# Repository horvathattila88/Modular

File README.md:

# Modular
Modular synth stuff

Most of these are designs from other people, i've just redrawn them to fit into a eurorack system. The PCB's are smaller than 100x100mm, so it's easier to have them manufactured, pick any of your favourite manufacturers. The plans are in EAGLE 7.4 format, you can generate gerbers from there, according to the manufacturers needs. 
I have uploaded this for hobbyists, i don't make any money out of it, you shouldn't sell the boards! 
The MFOS ones are designed by Ray Wilson - Music From Outer Space, please respect his heritage. 
Yusynth is Yves Usson

The PSU is my own design, (simple as Trump) you'll need a transformer with 2x12V AC secondaries, or 1x15V AC, connected to the center and one of the AC inputs. Two way, or one way rectifier, you choose, i like to use 2-way, with a center tap transformer. 
Don't use it for more than 7-800mA, for example, one bigger transformer on the bottom of the case and one PSU in each row... Install the SMD or the TH LED's, not both. There is no 5V rail, nor CV, or Gate, as i'm not using those, and found it's a bad solution. 
There is also a distribution board, it can be cut into more strips if needed. LED's and filtering caps can be soldered on those too, but not necessary. 

Part numbering is (most of the time) the same as in the MFOS webpage, you'll need to read through the documentation there. 
There are some exceptions, like the ringmodulator, i've made a dual ringmod without the VC sine osc, and the simple osc on a standalone module. It's quite straightforward though. 

Here is the status of the modules: 

PSU, rails - Tested OK, pinouts are the same as on the modules, be careful when making ribbon cables! 

MFOS VCF 12dBi state variable - Tested OK (sounds sweet) 

MFOS VC LFO - Tested OK 

MFOS VCO - Tested, not calibrated yet

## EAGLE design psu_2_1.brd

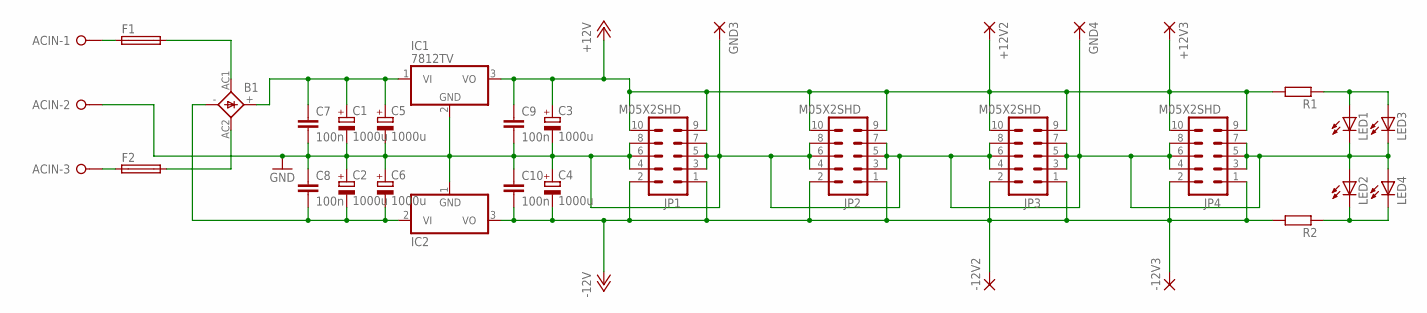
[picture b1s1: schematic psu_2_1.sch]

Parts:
+12V2, +12V3: 2,54/1,0
-12V2, -12V3: 2,54/1,0
ACIN: W237-3E
B1: 2KBP
C1, C2, C3, C4, C5, C6: 1000u; E3,5-10
C7, C8, C9, C10: 100n; C1206K
F1, F2: 19560
GND3, GND4: 2,54/1,0
IC1: 7812TV; TO220V
IC2: 7912TV; TO220V
JP1, JP2, JP3, JP4: M05X2SHD; 2X5-SHROUDED
LED1, LED2: LED3MM
LED3, LED4: LEDCHIPLED_1206; CHIPLED_1206
R1, R2: R-EU_M1206; M1206

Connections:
+12V: +12V2.1, +12V3.1, C3.+, C9.1, IC1.3 (VO), JP1.9, JP1.10, JP2.9, JP2.10, JP3.9, JP3.10, JP4.9, JP4.10, R1.2
-12V: -12V2.1, -12V3.1, C4.-, C10.2, IC2.3 (VO), JP1.1, JP1.2, JP2.1, JP2.2, JP3.1, JP3.2, JP4.1, JP4.2, R2.2
GND: ACIN.2, C1.-, C2.+, C3.-, C4.+, C5.-, C6.+, C7.2, C8.1, C9.2, C10.1, GND3.1, GND4.1, IC1.2 (GND), IC2.1 (GND), JP1.3, JP1.4, JP1.5, JP1.6, JP1.7, JP1.8, JP2.3, JP2.4, JP2.5, JP2.6, JP2.7, JP2.8, JP3.3, JP3.4, JP3.5, JP3.6, JP3.7, JP3.8, JP4.3, JP4.4, JP4.5, JP4.6, JP4.7, JP4.8, LED1.K (C), LED2.A, LED3.C, LED4.A
unnamed: LED2.K (C), LED4.C, R2.1
unnamed: LED1.A, LED3.A, R1.1
unnamed: B1.-, C2.-, C6.-, C8.2, IC2.2 (VI)
unnamed: B1.+, C1.+, C5.+, C7.1, IC1.1 (VI)
unnamed: B1.AC1, F1.2
unnamed: B1.AC2, F2.2
unnamed: ACIN.1, F1.1
unnamed: ACIN.3, F2.1

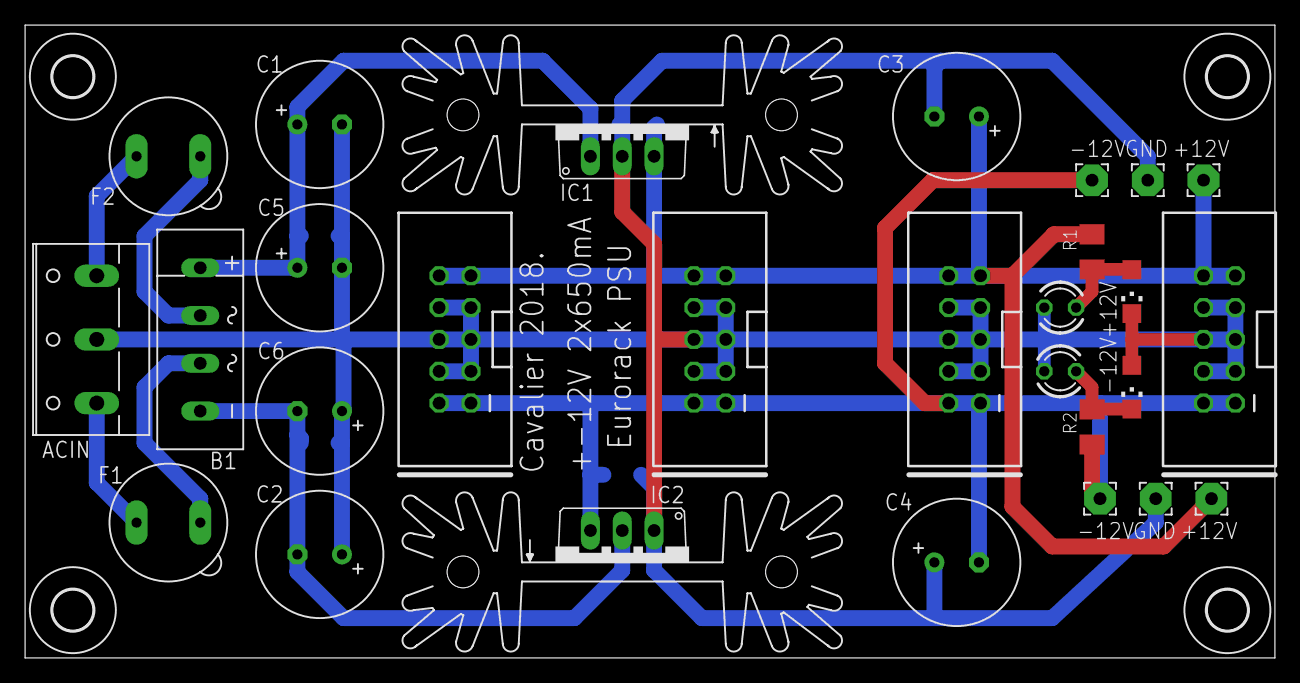
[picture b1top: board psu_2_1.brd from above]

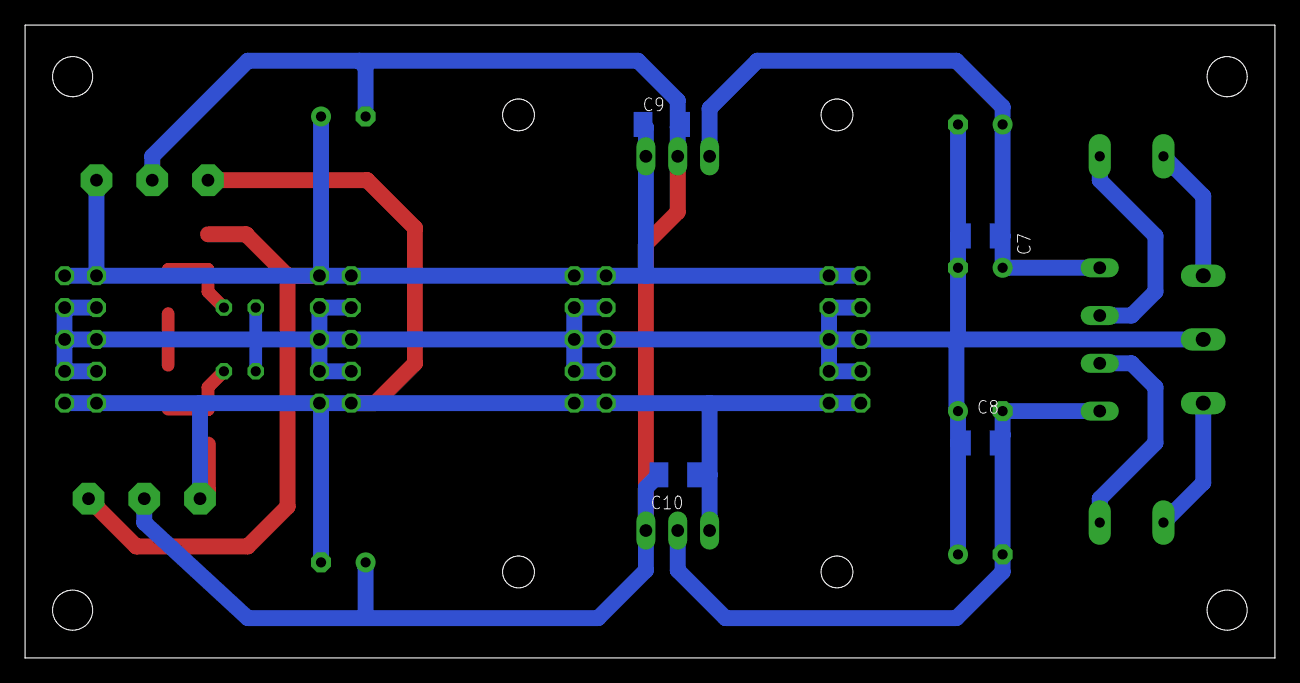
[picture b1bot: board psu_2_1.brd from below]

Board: 2 copper layers, 99.7 x 50.5 mm, 38 parts (4 on the bottom side), 11 nets.

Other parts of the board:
U$1, U$2, U$3, U$4: 3,2
U$5, U$7: SK104

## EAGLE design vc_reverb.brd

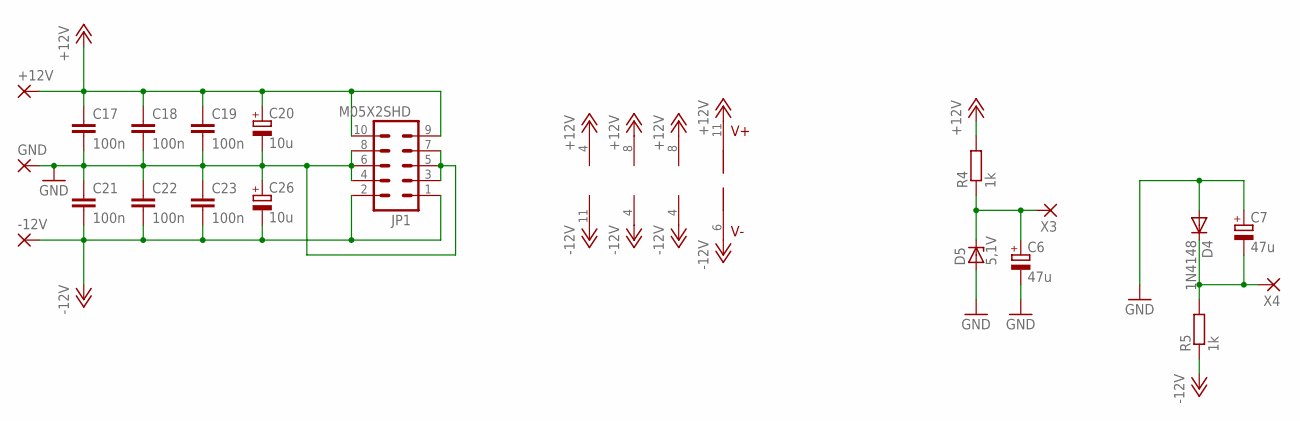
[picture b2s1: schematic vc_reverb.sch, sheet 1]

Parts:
+12V: 2,54/1,0
-12V: 2,54/1,0
C6, C7: 47u; E2-5
C17, C19, C21, C23: 100n; C025-025X050
C18, C22: 100n; C050-035X075
C20, C26: 10u; E2-5
D4: 1N4148; DO35-7
D5: 5,1V; DO34Z7
GND: 2,54/1,0
IC3: TL074P; DIL14
IC4: LM13700N; DIL16
IC5, IC6: TL072P; DIL08
JP1: M05X2SHD; 2X5-SHROUDED
R4, R5: 1k; 0309V
X3, X4: 2,54/1,0

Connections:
+12V: +12V.1, C17.1, C18.1, C19.1, C20.+, IC3.4 (V+), IC4.11 (V+), IC5.8 (V+), IC6.8 (V+), JP1.9, JP1.10, R4.2; also elsewhere on the board
-12V: -12V.1, C21.2, C22.2, C23.2, C26.-, IC3.11 (V-), IC4.6 (V-), IC5.4 (V-), IC6.4 (V-), JP1.1, JP1.2, R5.1; also elsewhere on the board
GND: C6.-, C7.+, C17.2, C18.2, C19.2, C20.-, C21.1, C22.1, C23.1, C26.+, D4.A, D5.A, GND.1, JP1.3, JP1.4, JP1.5, JP1.6, JP1.7, JP1.8; also elsewhere on the board
unnamed: C6.+, D5.C, R4.1, X3.1
unnamed: C7.-, D4.C, R5.2, X4.1

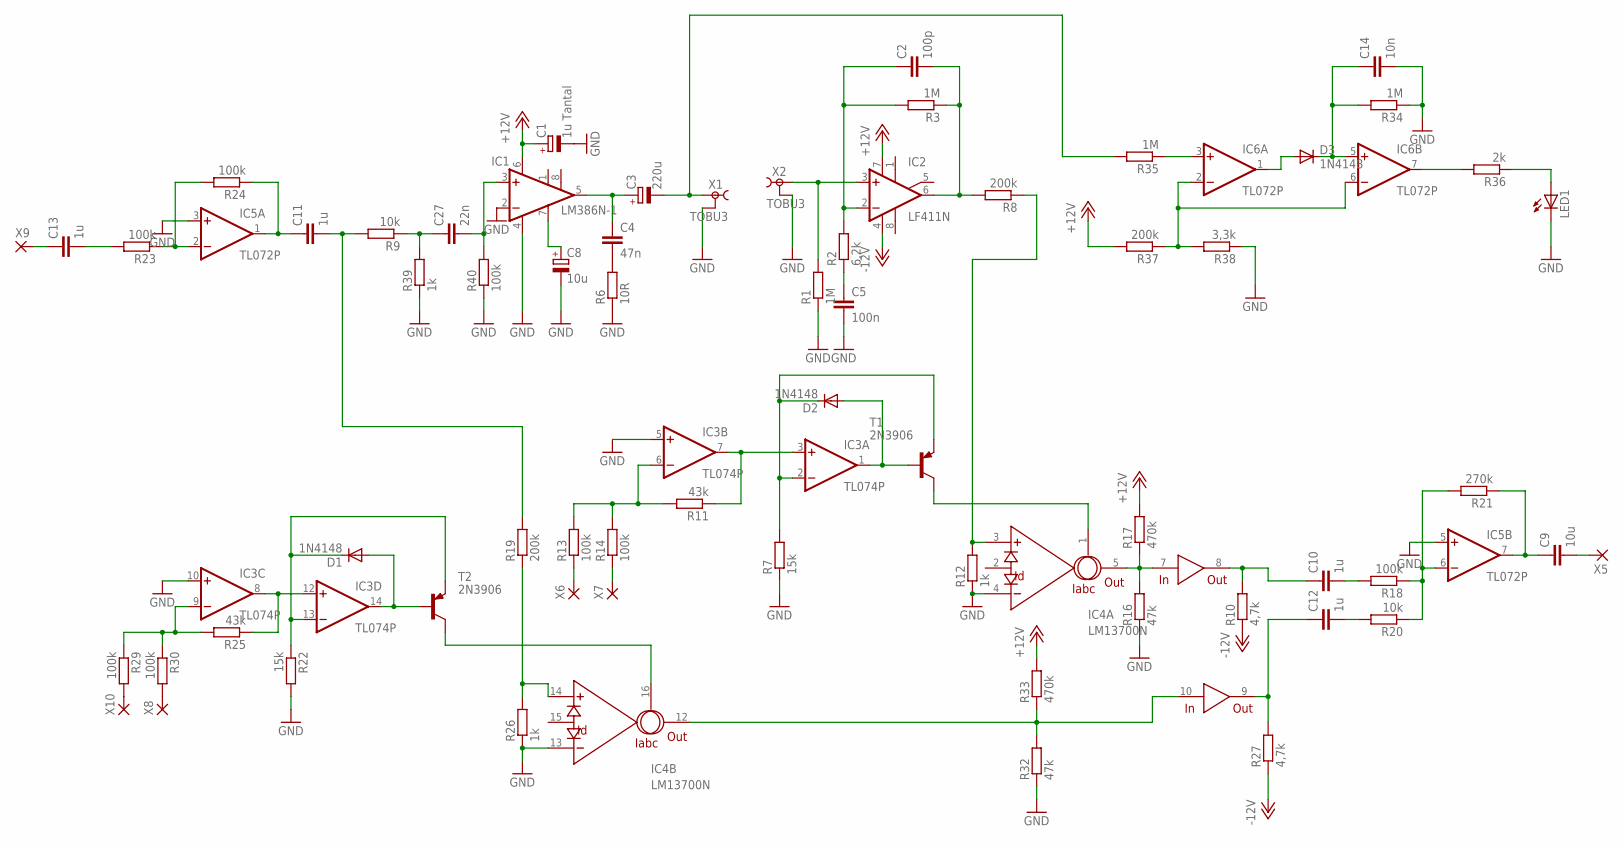
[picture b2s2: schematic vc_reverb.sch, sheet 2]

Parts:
C1: 1u Tantal; E2-5
C2: 100p; C050-035X075
C3: 220u; E3,5-8
C4: 47n; C050-035X075
C5: 100n; C050-035X075
C8: 10u; E2-5
C9: 10u; C050-075X075
C10, C11, C12, C13: 1u; C050-050X075
C14: 10n; C050-030X075
C27: 22n; C050-035X075
D1, D2, D3: 1N4148; DO35-7
IC1: LM386N-1; DIL08
IC2: LF411N; DIL08
IC3: TL074P; DIL14
IC4: LM13700N; DIL16
IC5, IC6: TL072P; DIL08
LED1: LED5MM
R1, R3, R34, R35: 1M; 0309V
R2: 6,2k; 0309V
R6: 10R; 0309V
R7, R22: 15k; 0309V
R8, R37: 200k; 0309V
R9, R20: 10k; 0309V
R10, R27: 4,7k; 0309V
R11, R25: 43k; 0309V
R12, R26, R39: 1k; 0309V
R13, R14, R18, R23, R24, R29, R30, R40: 100k; 0309V
R16, R32: 47k; 0309V
R17, R33: 470k; 0309V
R19: 200k; 0309/10
R21: 270k; 0309V
R36: 2k; 0309V
R38: 3,3k; 0309V
T1, T2: 2N3906; TO92-EBC
X1, X2: TOBU3
X5, X6, X7, X8, X9, X10: 2,54/1,0

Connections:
+12V: C1.+, IC1.6 (VS), IC2.7 (V+), R17.2, R33.2, R37.2; also elsewhere on the board
-12V: IC2.4 (V-), R10.1, R27.1; also elsewhere on the board
GND: C1.-, C5.2, C8.-, C14.2, IC1.2 (-IN), IC1.4 (GND), IC3.5 (+IN), IC3.10 (+IN), IC4.4 (-IN), IC4.13 (-IN), IC5.3 (+IN), IC5.5 (+IN), LED1.K (C), R1.1, R6.1, R7.1, R12.1, R16.1, R22.2, R26.1, R32.1, R34.1, R38.1, R39.1, R40.1, X1.2, X1.2@1 (2), X1.2@2 (2), X2.2, X2.2@1 (2), X2.2@2 (2); also elsewhere on the board
unnamed: D3.A, IC6.1 (OUT)
unnamed: C14.1, D3.C, IC6.5 (+IN), R34.2
unnamed: IC6.7 (OUT), R36.2
unnamed: LED1.A, R36.1
unnamed: IC6.3 (+IN), R35.1
unnamed: C3.+, C4.1, IC1.5 (OUT)
unnamed: IC6.2 (-IN), IC6.6 (-IN), R37.1, R38.2
unnamed: C8.+, IC1.7 (BYPASS)
unnamed: C4.2, R6.2
unnamed: C27.2, IC1.3 (+IN), R40.2
unnamed: C27.1, R9.1, R39.2
unnamed: IC2.3 (+IN), R1.2, X2.1
unnamed: C2.1, IC2.2 (-IN), R2.2, R3.2
unnamed: C5.1, R2.1
unnamed: C2.2, IC2.6 (OUT), R3.1, R8.2
unnamed: IC5.2 (-IN), R23.1, R24.2
unnamed: C11.1, IC5.1 (OUT), R24.1
unnamed: C13.2, R23.2
unnamed: C13.1, X9.1
unnamed: C11.2, R9.2, R19.2
unnamed: C12.2, R20.2
unnamed: C10.2, R18.2
unnamed: IC5.6 (-IN), R18.1, R20.1, R21.2
unnamed: C9.1, IC5.7 (OUT), R21.1
unnamed: C9.2, X5.1
unnamed: C12.1, IC4.9 (OUT), R27.2
unnamed: C10.1, IC4.8 (OUT), R10.2
unnamed: IC4.5 (OUT), IC4.7 (IN), R16.2, R17.1
unnamed: IC4.3 (+IN), R8.1, R12.2
unnamed: D2.A, IC3.1 (OUT), T1.B
unnamed: IC4.10 (IN), IC4.12 (OUT), R32.2, R33.1
unnamed: IC4.14 (+IN), R19.1, R26.2
unnamed: D2.C, IC3.2 (-IN), R7.2, T1.E
unnamed: IC3.3 (+IN), IC3.7 (OUT), R11.1
unnamed: IC3.6 (-IN), R11.2, R13.2, R14.2
unnamed: R14.1, X7.1
unnamed: R13.1, X6.1
unnamed: IC4.1 (IABC), T1.C
unnamed: D1.A, IC3.14 (OUT), T2.B
unnamed: D1.C, IC3.13 (-IN), R22.1, T2.E
unnamed: IC3.8 (OUT), IC3.12 (+IN), R25.1
unnamed: IC3.9 (-IN), R25.2, R29.1, R30.1
unnamed: R30.2, X8.1
unnamed: R29.2, X10.1
unnamed: IC4.16 (IABC), T2.C
OL: C3.-, R35.2, X1.1

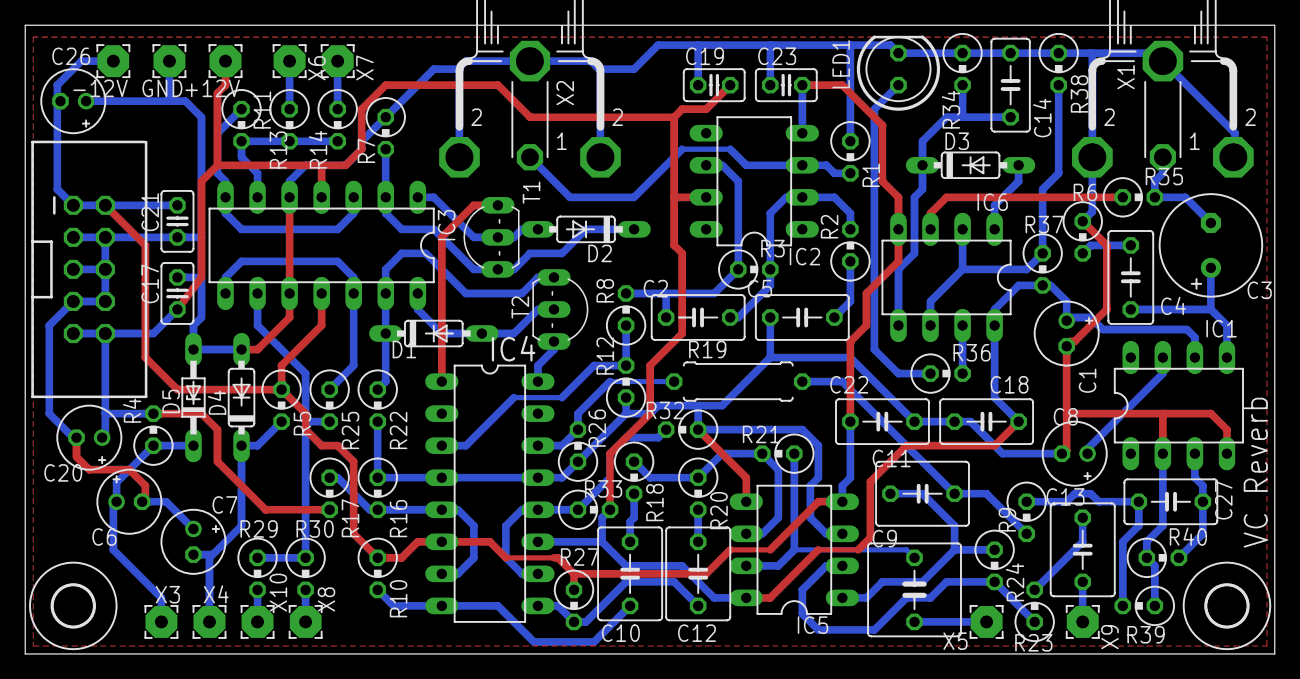
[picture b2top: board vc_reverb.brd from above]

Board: 2 copper layers, 99.0 x 49.8 mm, 90 parts (0 on the bottom side), 51 nets.

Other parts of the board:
U$1, U$2: 3,2

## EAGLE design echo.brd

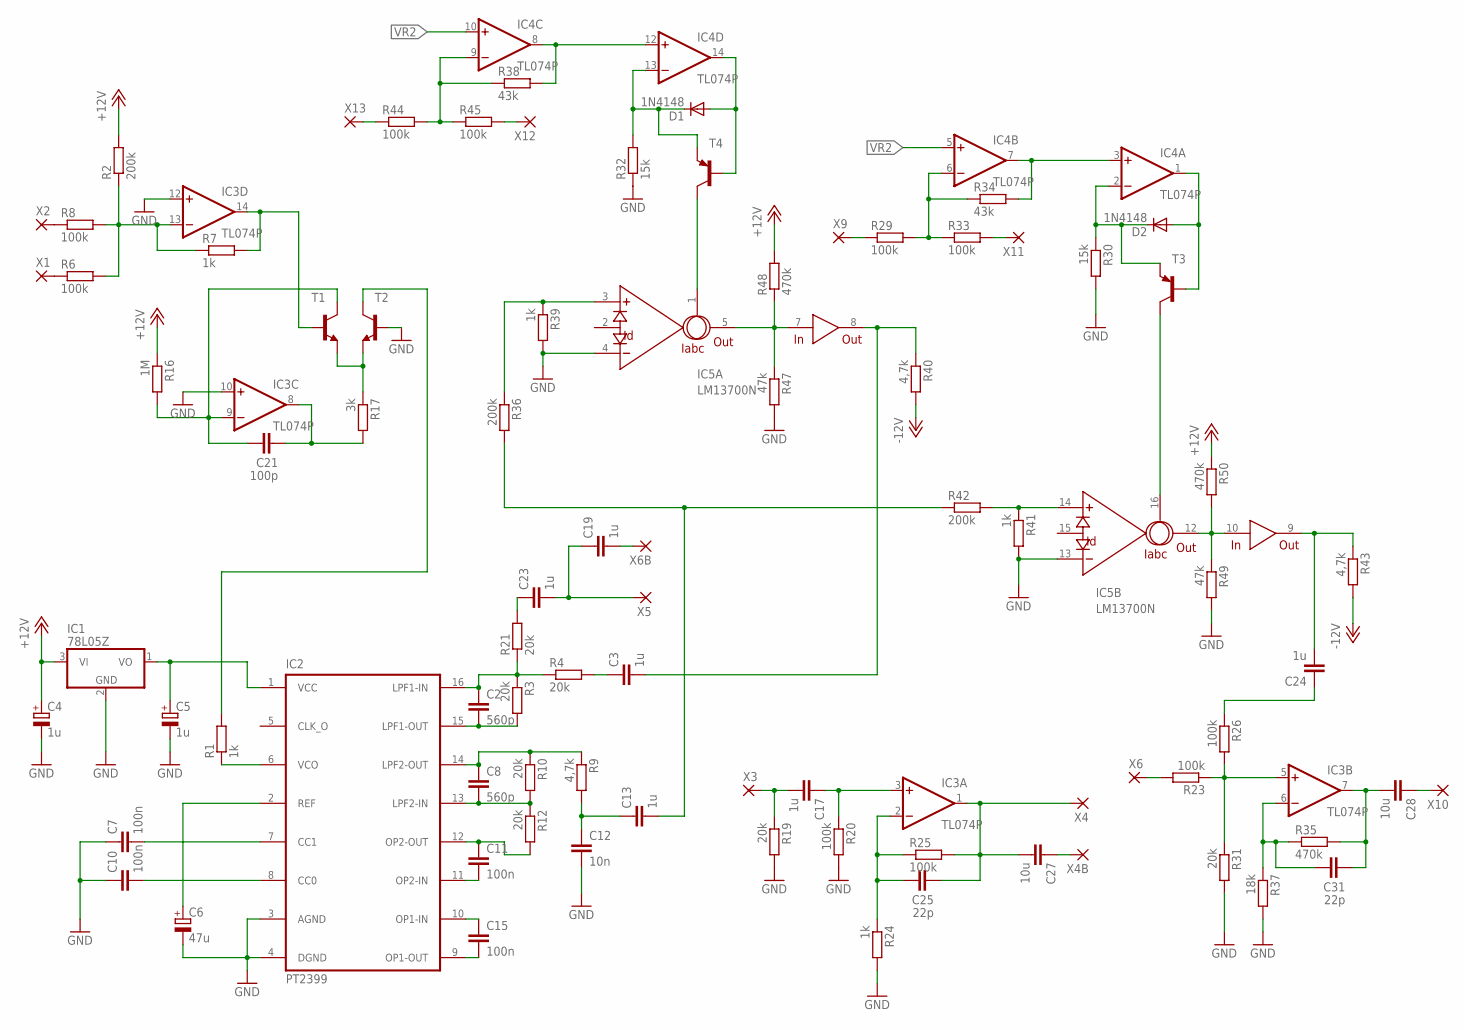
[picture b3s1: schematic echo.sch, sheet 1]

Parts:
C2, C8: 560p; C050-035X075
C3, C13, C17, C19, C23, C24: 1u; C050-055X075
C4, C5: 1u; E2-5
C6: 47u; E2-5
C7, C10, C11, C15: 100n; C050-035X075
C12: 10n; C050-035X075
C21: 100p; C025-025X050
C25, C31: 22p; C025-025X050
C27, C28: 10u; C050-055X075
D1, D2: 1N4148; DO35-7
IC1: 78L05Z; TO92
IC2: PT2399; DIL16
IC3, IC4: TL074P; DIL14
IC5: LM13700N; DIL16
R1, R7, R24, R39, R41: 1k; 0309V
R2, R36, R42: 200k; 0309V
R3, R4, R10, R12, R19, R21, R31: 20k; 0309V
R6, R8, R20, R23, R25, R26, R29, R33, R44, R45: 100k; 0309V
R9, R40, R43: 4,7k; 0309V
R16: 1M; 0309V
R17: 3k; 0309V
R30, R32: 15k; 0309V
R34, R38: 43k; 0309V
R35, R48, R50: 470k; 0309V
R37: 18k; 0309V
R47, R49: 47k; 0309V
T1, T2: 2N3904-NPN-TO92-EBC; TO92-EBC
T3, T4: 2N3906-PNP-TO92-EBC; TO92-EBC
X1, X2, X3, X4, X4B, X5, X6, X6B, X9, X10, X11, X12, X13: 2,54/1,0

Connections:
+12V: C4.+, IC1.3 (VI), R2.2, R16.1, R48.2, R50.1; also elsewhere on the board
-12V: R40.2, R43.2; also elsewhere on the board
GND: C4.-, C5.-, C6.-, C7.1, C10.1, C12.2, IC1.2 (GND), IC2.3 (AGND), IC2.4 (DGND), IC3.10 (+IN), IC3.12 (+IN), IC5.4 (-IN), IC5.13 (-IN), R19.2, R20.2, R24.2, R30.2, R31.2, R32.1, R37.2, R39.2, R41.2, R47.2, R49.2, T2.B; also elsewhere on the board
unnamed: C7.2, IC2.7 (CC1)
unnamed: C10.2, IC2.8 (CC0)
unnamed: C5.+, IC1.1 (VO), IC2.1 (VCC)
unnamed: C15.1, IC2.10 (OP1-IN)
unnamed: C6.+, IC2.2 (REF)
unnamed: C15.2, IC2.9 (OP1-OUT)
unnamed: C11.2, IC2.11 (OP2-IN)
unnamed: C11.1, IC2.12 (OP2-OUT), R12.2
unnamed: C19.2, X6B.1
unnamed: C2.2, IC2.15 (LPF1-OUT), R3.2
unnamed: C8.1, IC2.14 (LPF2-OUT), R9.1, R10.1
unnamed: C8.2, IC2.13 (LPF2-IN), R10.2, R12.1
unnamed: IC2.6 (VCO), R1.1
unnamed: C3.1, R4.2
unnamed: C12.1, C13.1, R9.2
unnamed: C23.1, R21.2
unnamed: C2.1, IC2.16 (LPF1-IN), R3.1, R4.1, R21.1
unnamed: C19.1, C23.2, X5.1
unnamed: IC3.5 (+IN), R23.1, R26.2, R31.1
unnamed: R23.2, X6.1
unnamed: R44.1, X13.1
unnamed: IC4.9 (-IN), R38.1, R44.2, R45.1
unnamed: R45.2, X12.1
unnamed: IC4.8 (OUT), IC4.12 (+IN), R38.2
unnamed: D1.A, IC4.14 (OUT), T4.B
unnamed: D1.C, IC4.13 (-IN), R32.2, T4.E
unnamed: IC5.5 (OUT), IC5.7 (IN), R47.1, R48.1
unnamed: C24.2, IC5.9 (OUT), R43.1
unnamed: IC5.3 (+IN), R36.1, R39.1
unnamed: C13.2, R36.2, R42.1
unnamed: C3.2, IC5.8 (OUT), R40.1
unnamed: IC5.1 (IABC), T4.C
unnamed: IC5.10 (IN), IC5.12 (OUT), R49.1, R50.2
unnamed: IC5.14 (+IN), R41.1, R42.2
unnamed: IC4.3 (+IN), IC4.7 (OUT), R34.2
unnamed: R29.1, X9.1
unnamed: R33.2, X11.1
unnamed: C25.1, IC3.2 (-IN), R24.1, R25.1
unnamed: IC4.6 (-IN), R29.2, R33.1, R34.1
unnamed: D2.A, IC4.1 (OUT), T3.B
unnamed: D2.C, IC4.2 (-IN), R30.1, T3.E
unnamed: IC5.16 (IABC), T3.C
unnamed: C24.1, R26.1
unnamed: C31.1, IC3.6 (-IN), R35.1, R37.1
unnamed: C28.2, C31.2, IC3.7 (OUT), R35.2
unnamed: C28.1, X10.1
unnamed: C25.2, C27.2, IC3.1 (OUT), R25.2, X4.1
unnamed: C27.1, X4B.1
unnamed: C17.2, R19.1, X3.1
unnamed: C17.1, IC3.3 (+IN), R20.1
unnamed: C21.1, IC3.9 (-IN), R16.2, T1.C
unnamed: C21.2, IC3.8 (OUT), R17.2
unnamed: R17.1, T1.E, T2.E
unnamed: IC3.14 (OUT), R7.2, T1.B
unnamed: R1.2, T2.C
unnamed: IC3.13 (-IN), R2.1, R6.2, R7.1, R8.2
unnamed: R6.1, X1.1
unnamed: R8.1, X2.1
VR2: IC4.5 (+IN), IC4.10 (+IN); also elsewhere on the board

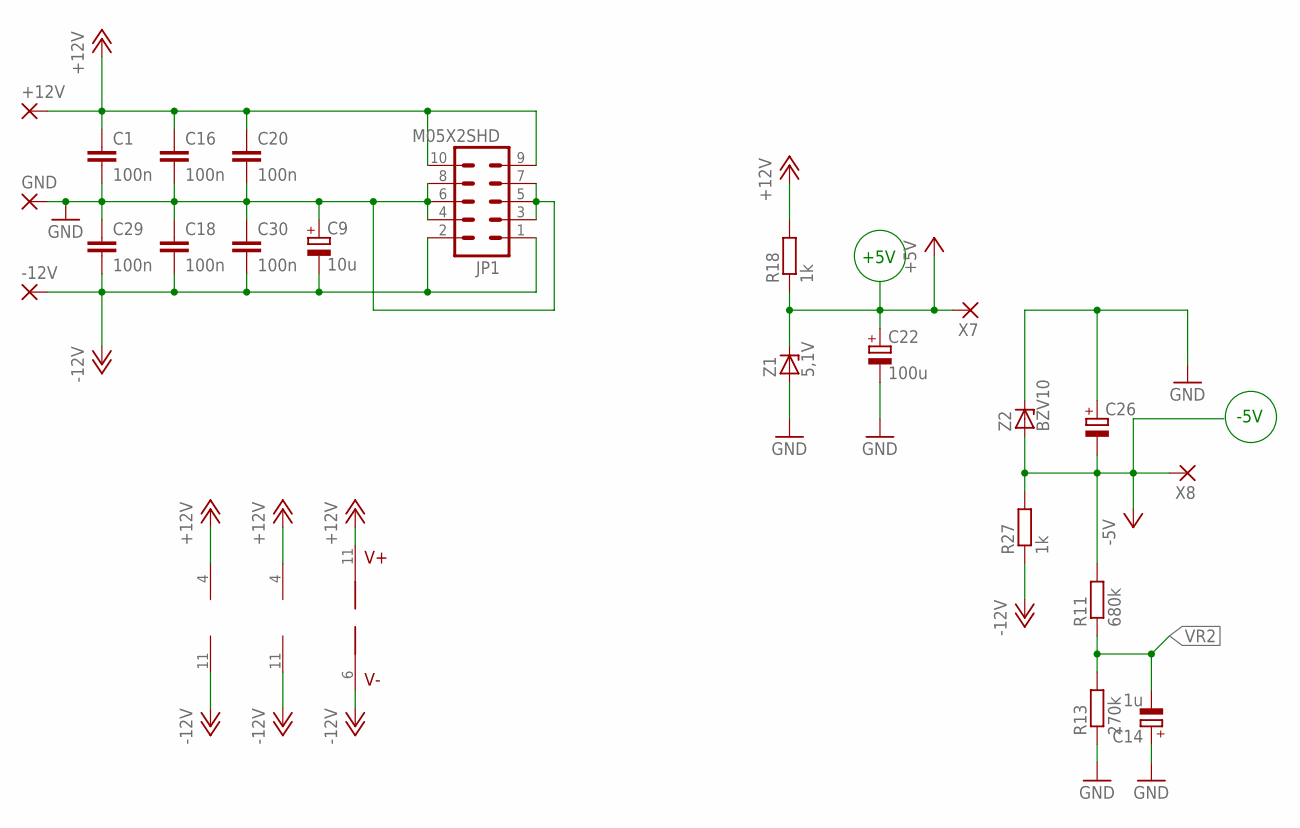
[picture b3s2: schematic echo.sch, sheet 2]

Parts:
+12V: 2,54/1,0
-12V: 2,54/1,0
C1, C16, C18, C20, C29, C30: 100n; C025-025X050
C9: 10u; E2-5
C14: 1u; E2-5
C22: 100u; E2-5
C26: CPOL-EUE2-5; E2-5
GND: 2,54/1,0
IC3, IC4: TL074P; DIL14
IC5: LM13700N; DIL16
JP1: M05X2SHD; 2X5-SHROUDED
R11: 680k; 0309V
R13: 270k; 0309V
R18, R27: 1k; 0309V
X7, X8: 2,54/1,0
Z1: 5,1V; DO34Z7
Z2: BZV10; DO34Z7

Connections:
+5V: C22.+, R18.1, X7.1, Z1.C
+12V: +12V.1, C1.1, C16.1, C20.1, IC3.4 (V+), IC4.4 (V+), IC5.11 (V+), JP1.9, JP1.10, R18.2; also elsewhere on the board
-5V: C26.-, R11.2, R27.2, X8.1, Z2.A
-12V: -12V.1, C9.-, C18.2, C29.2, C30.2, IC3.11 (V-), IC4.11 (V-), IC5.6 (V-), JP1.1, JP1.2, R27.1; also elsewhere on the board
GND: C1.2, C9.+, C14.+, C16.2, C18.1, C20.2, C22.-, C26.+, C29.1, C30.1, GND.1, JP1.3, JP1.4, JP1.5, JP1.6, JP1.7, JP1.8, R13.1, Z1.A, Z2.C; also elsewhere on the board
VR2: C14.-, R11.1, R13.2; also elsewhere on the board

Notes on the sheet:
-5V
+5V

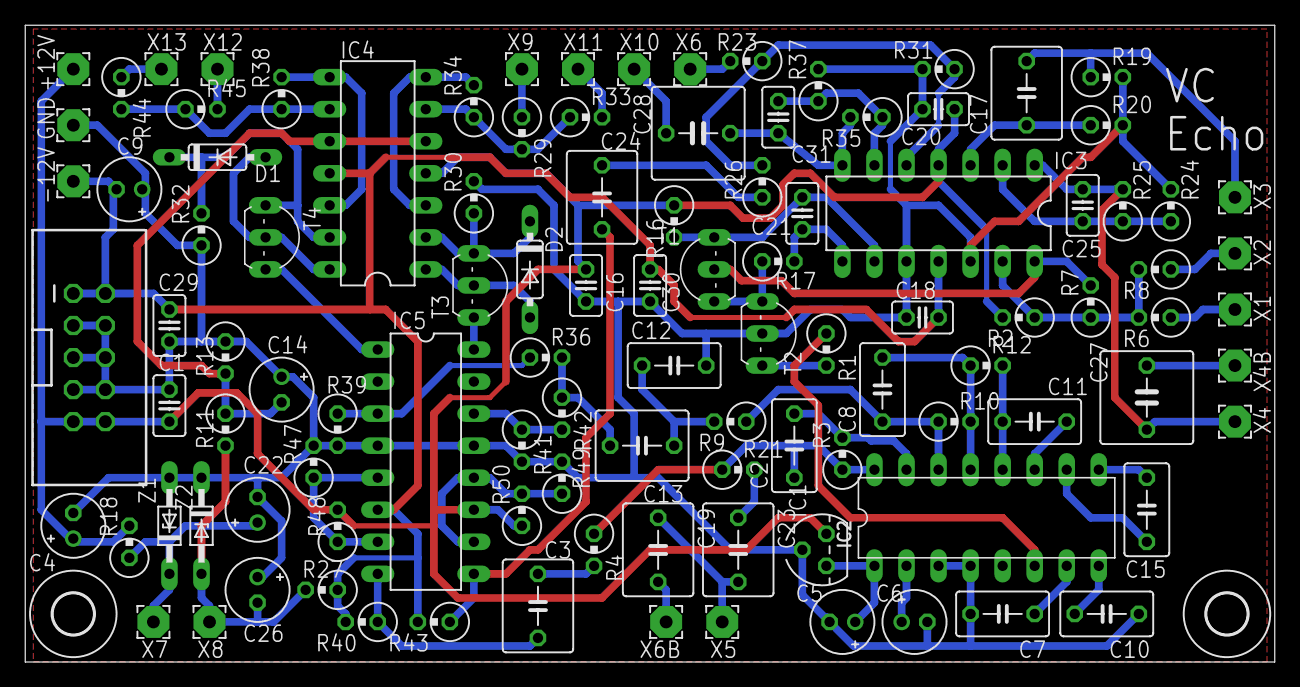
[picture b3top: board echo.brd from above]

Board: 2 copper layers, 99.0 x 50.5 mm, 109 parts (0 on the bottom side), 64 nets.

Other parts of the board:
U$1, U$2: 3,2

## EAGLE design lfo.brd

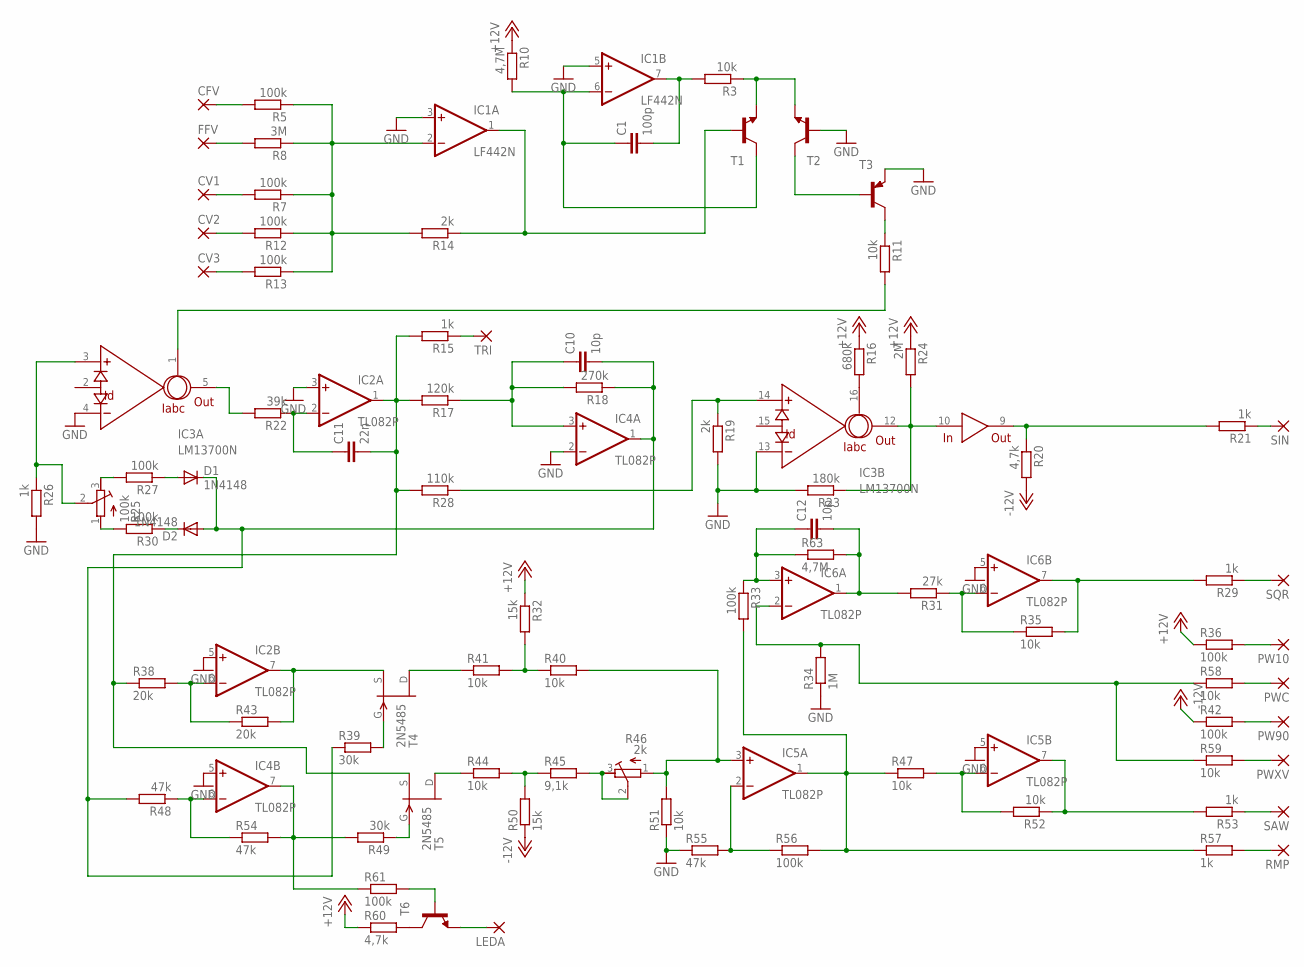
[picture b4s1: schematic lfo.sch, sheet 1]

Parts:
C1: 100p; C050-035X075
C10, C12: 10p; C050-035X075
C11: 22n; C050-035X075
CFV: 2,54/1,0
CV1, CV2, CV3: 2,54/1,0
D1, D2: 1N4148; DO35-7
FFV: 2,54/1,0
IC1: LF442N; DIL08
IC2, IC4, IC5, IC6: TL082P; DIL08
IC3: LM13700N; DIL16
LEDA: 2,54/1,0
PW10, PW90: 2,54/1,0
PWC: 2,54/1,0
PWXV: 2,54/1,0
R3, R11, R35, R40, R41, R44, R47, R51, R52, R58, R59: 10k; 0309V
R5, R7, R12, R13, R27, R30, R33, R36, R42, R56, R61: 100k; 0309V
R8: 3M; 0309V
R10: 4,7M; 0309V
R14, R19: 2k; 0309V
R15, R21, R26, R29, R53, R57: 1k; 0309V
R16: 680k; 0309V
R17: 120k; 0309V
R18: 270k; 0309V
R20, R60: 4,7k; 0309V
R22: 39k; 0309V
R23: 180k; 0309V
R24: 2M; 0309V
R25: 100k; RTRIM64W
R28: 110k; 0309V
R31: 27k; 0309V
R32, R50: 15k; 0309V
R34: 1M; 0309V
R38, R43: 20k; 0309V
R39, R49: 30k; 0309V
R45: 9,1k; 0309V
R46: 2k; RTRIM64W
R48, R54, R55: 47k; 0309V
R63: 4,7M; 0309/10
RMP: 2,54/1,0
SAW: 2,54/1,0
SIN: 2,54/1,0
SQR: 2,54/1,0
T1, T2, T6: 2N3904-NPN-TO92-EBC; TO92-EBC
T3: 2N3906-PNP-TO92-EBC; TO92-EBC
T4, T5: 2N5485; TO92-
TRI: 2,54/1,0

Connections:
+12V: R10.1, R16.1, R24.1, R32.1, R36.1, R60.1; also elsewhere on the board
-12V: R20.2, R42.1, R50.1; also elsewhere on the board
GND: IC1.3 (+IN), IC1.5 (+IN), IC2.3 (+IN), IC2.5 (+IN), IC3.4 (-IN), IC3.13 (-IN), IC4.2 (-IN), IC4.5 (+IN), IC5.5 (+IN), IC6.5 (+IN), R19.2, R23.2, R26.2, R34.1, R51.1, R55.1, T2.B, T3.E; also elsewhere on the board
unnamed: FFV.1, R8.2
unnamed: CFV.1, R5.2
unnamed: IC1.1 (OUT), R14.1, T1.B
unnamed: CV1.1, R7.2
unnamed: CV2.1, R12.2
unnamed: CV3.1, R13.2
unnamed: IC1.2 (-IN), R5.1, R7.1, R8.1, R12.1, R13.1, R14.2
unnamed: C1.1, IC1.6 (-IN), R10.2, T1.C
unnamed: C1.2, IC1.7 (OUT), R3.2
unnamed: R3.1, T1.E, T2.E
unnamed: T2.C, T3.B
unnamed: R11.1, T3.C
unnamed: IC3.1 (IABC), R11.2
unnamed: IC3.3 (+IN), R25.2 (S), R26.1
unnamed: IC3.14 (+IN), R19.1, R28.1
unnamed: R25.3 (E), R27.2
unnamed: R25.1 (A), R30.2
unnamed: D2.C, R30.1
unnamed: D1.A, R27.1
unnamed: C10.2, D1.C, D2.A, IC4.1 (OUT), R18.1, R39.1, R48.2
unnamed: IC3.5 (OUT), R22.2
unnamed: C11.1, IC2.2 (-IN), R22.1
unnamed: C11.2, IC2.1 (OUT), R15.2, R17.2, R28.2, R38.1, T5.2 (S)
unnamed: C10.1, IC4.3 (+IN), R17.1, R18.2
unnamed: R15.1, TRI.1
unnamed: R21.1, SIN.1
unnamed: IC3.16 (IABC), R16.2
unnamed: IC3.10 (IN), IC3.12 (OUT), R23.1, R24.2
unnamed: IC3.9 (OUT), R20.1, R21.2
unnamed: IC2.6 (-IN), R38.2, R43.1
unnamed: IC2.7 (OUT), R43.2, T4.2 (S)
unnamed: IC4.6 (-IN), R48.1, R54.1
unnamed: IC4.7 (OUT), R49.2, R54.2, R61.1
unnamed: R39.2, T4.1 (G)
unnamed: R60.2, T6.C
unnamed: R41.1, T4.3 (D)
unnamed: R32.2, R40.1, R41.2
unnamed: IC5.3 (+IN), R40.2, R46.1 (A), R51.2
unnamed: R49.1, T5.1 (G)
unnamed: R44.1, T5.3 (D)
unnamed: R44.2, R45.1, R50.2
unnamed: R45.2, R46.2 (S), R46.3 (E)
unnamed: R61.2, T6.B
unnamed: LEDA.1, T6.E
unnamed: IC5.2 (-IN), R55.2, R56.1
unnamed: IC5.1 (OUT), R33.2, R47.1, R56.2, R57.1
unnamed: R57.2, RMP.1
unnamed: C12.2, IC6.1 (OUT), R31.2, R63.2
unnamed: C12.1, IC6.3 (+IN), R33.1, R63.1
unnamed: PWXV.1, R59.2
unnamed: IC6.2 (-IN), R34.2, R58.1, R59.1
unnamed: PW90.1, R42.2
unnamed: PWC.1, R58.2
unnamed: PW10.1, R36.2
unnamed: IC6.6 (-IN), R31.1, R35.1
unnamed: IC6.7 (OUT), R29.2, R35.2
unnamed: R29.1, SQR.1
unnamed: IC5.6 (-IN), R47.2, R52.2
unnamed: IC5.7 (OUT), R52.1, R53.2
unnamed: R53.1, SAW.1

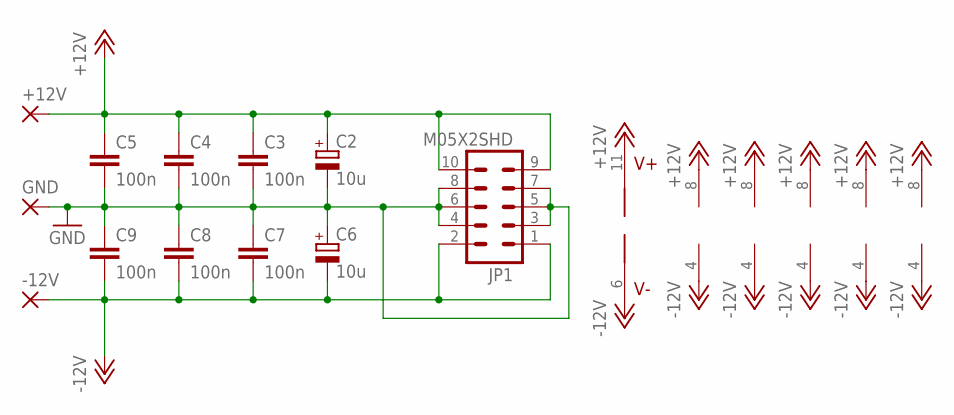
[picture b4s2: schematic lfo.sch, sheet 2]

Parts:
+12V: 2,54/1,0
-12V: 2,54/1,0
C2, C6: 10u; E3,5-8
C3, C4, C5, C7, C8, C9: 100n; C050-035X075
GND: 2,54/1,0
IC1: LF442N; DIL08
IC2, IC4, IC5, IC6: TL082P; DIL08
IC3: LM13700N; DIL16
JP1: M05X2SHD; 2X5-SHROUDED

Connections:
+12V: +12V.1, C2.+, C3.1, C4.1, C5.1, IC1.8 (V+), IC2.8 (V+), IC3.11 (V+), IC4.8 (V+), IC5.8 (V+), IC6.8 (V+), JP1.9, JP1.10; also elsewhere on the board
-12V: -12V.1, C6.-, C7.2, C8.2, C9.2, IC1.4 (V-), IC2.4 (V-), IC3.6 (V-), IC4.4 (V-), IC5.4 (V-), IC6.4 (V-), JP1.1, JP1.2; also elsewhere on the board
GND: C2.-, C3.2, C4.2, C5.2, C6.+, C7.1, C8.1, C9.1, GND.1, JP1.3, JP1.4, JP1.5, JP1.6, JP1.7, JP1.8; also elsewhere on the board

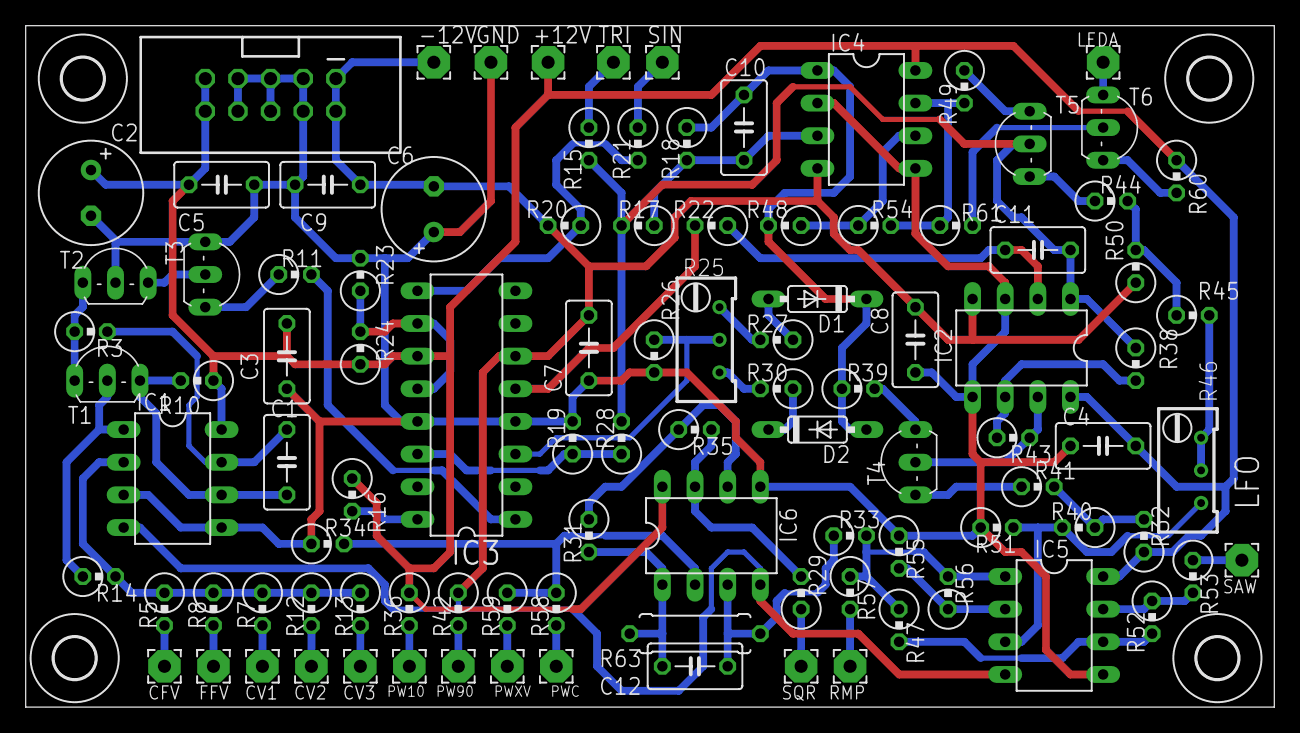
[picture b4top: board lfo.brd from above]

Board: 2 copper layers, 97.1 x 53.0 mm, 105 parts (0 on the bottom side), 63 nets.

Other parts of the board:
U$1, U$2, U$3, U$4: 3,2

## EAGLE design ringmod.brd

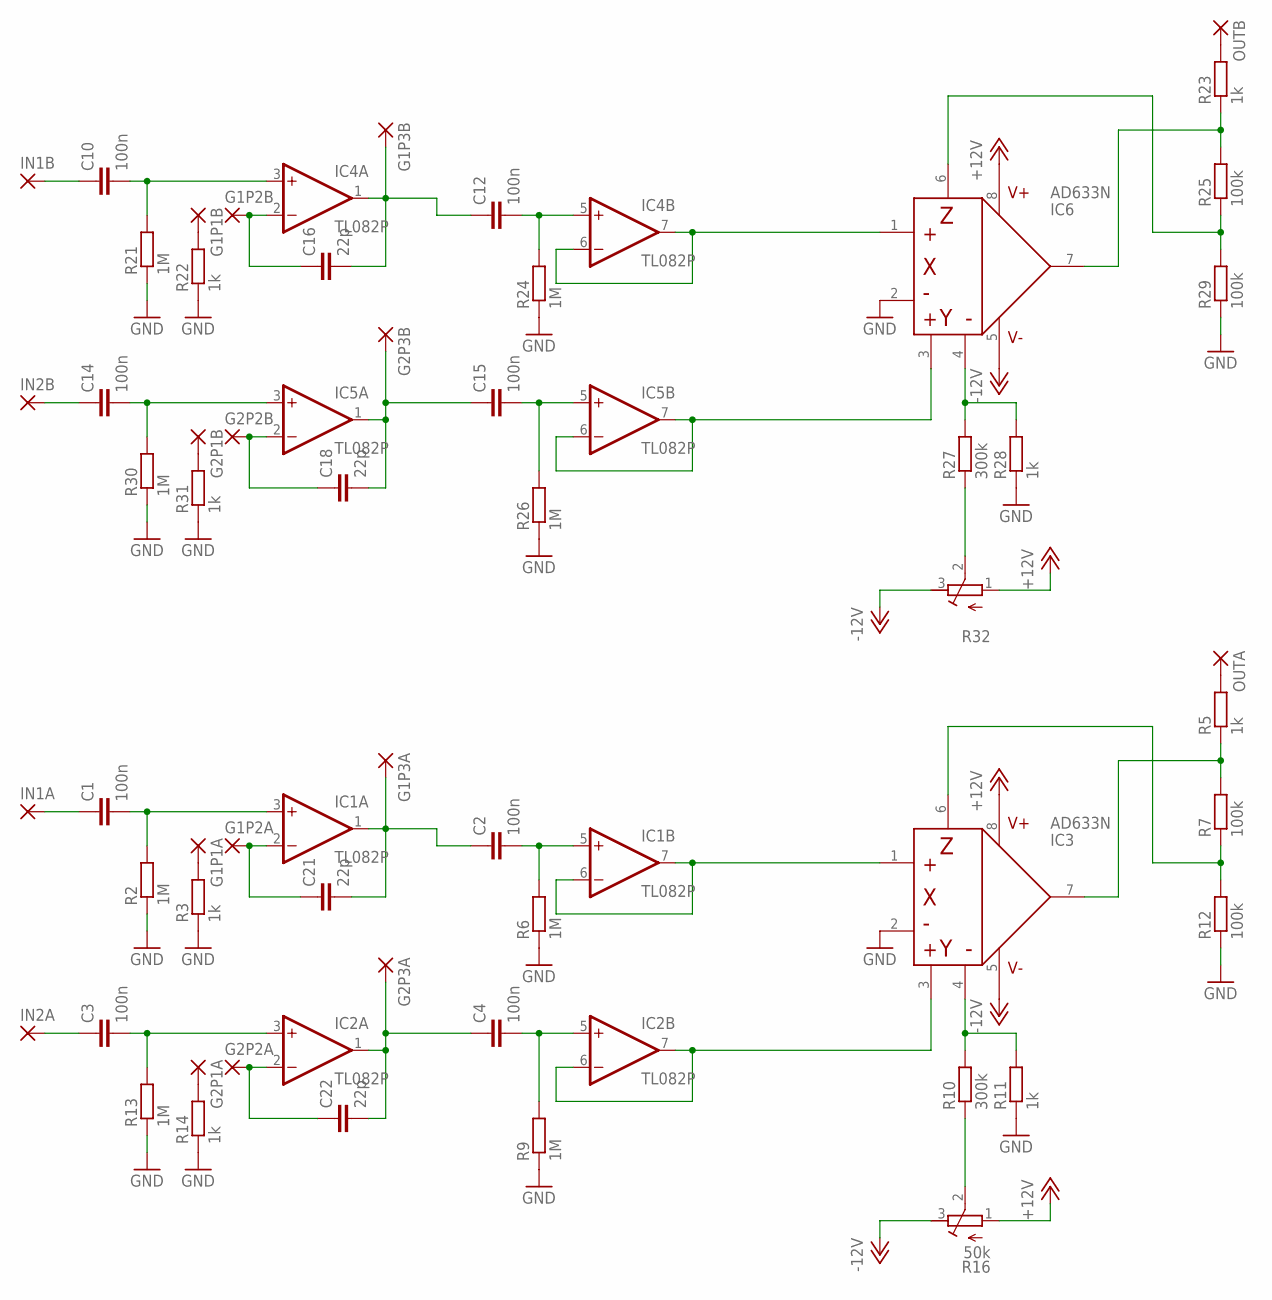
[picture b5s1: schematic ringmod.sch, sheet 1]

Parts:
C1, C2, C3, C4, C10, C12, C14, C15: 100n; C050-035X075
C16, C18, C21, C22: 22p; C050-035X075
G1P1A, G1P1B, G1P2A, G1P2B, G1P3A, G1P3B, G2P1A, G2P1B, G2P2A, G2P2B, G2P3A, G2P3B: 2,54/1,0
IC1, IC2, IC4, IC5: TL082P; DIL08
IC3, IC6: AD633N; DIL08
IN1A, IN1B, IN2A, IN2B: 2,54/1,0
OUTA: 2,54/1,0
OUTB: 2,54/1,0
R2, R6, R9, R13, R21, R24, R26, R30: 1M; 0309/10
R3, R5, R11, R14, R22, R23, R28, R31: 1k; 0309/10
R7, R12, R25, R29: 100k; 0309/10
R10, R27: 300k; 0309/10
R16: 50k; RTRIM64W
R32: R-TRIMM64W; RTRIM64W

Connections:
+12V: IC3.8, IC6.8, R16.1 (A), R32.1 (A); also elsewhere on the board
-12V: IC3.5, IC6.5, R16.3 (E), R32.3 (E); also elsewhere on the board
GND: IC3.2, IC6.2, R2.1, R3.1, R6.1, R9.1, R11.1, R12.1, R13.1, R14.1, R21.1, R22.1, R24.1, R26.1, R28.1, R29.1, R30.1, R31.1; also elsewhere on the board
unnamed: C2.1, C21.2, G1P3A.1, IC1.1 (OUT)
unnamed: C21.1, G1P2A.1, IC1.2 (-IN)
unnamed: G1P1A.1, R3.2
unnamed: C1.1, IN1A.1
unnamed: C1.2, IC1.3 (+IN), R2.2
unnamed: IC1.6 (-IN), IC1.7 (OUT), IC3.1
unnamed: C2.2, IC1.5 (+IN), R6.2
unnamed: C3.1, IN2A.1
unnamed: C3.2, IC2.3 (+IN), R13.2
unnamed: C4.1, C22.2, G2P3A.1, IC2.1 (OUT)
unnamed: C22.1, G2P2A.1, IC2.2 (-IN)
unnamed: G2P1A.1, R14.2
unnamed: C4.2, IC2.5 (+IN), R9.2
unnamed: IC2.6 (-IN), IC2.7 (OUT), IC3.3
unnamed: IC3.4, R10.2, R11.2
unnamed: R10.1, R16.2 (S)
unnamed: IC3.6, R7.1, R12.2
unnamed: IC3.7, R5.1, R7.2
unnamed: OUTA.1, R5.2
unnamed: C12.1, C16.2, G1P3B.1, IC4.1 (OUT)
unnamed: C16.1, G1P2B.1, IC4.2 (-IN)
unnamed: G1P1B.1, R22.2
unnamed: C10.1, IN1B.1
unnamed: C10.2, IC4.3 (+IN), R21.2
unnamed: IC4.6 (-IN), IC4.7 (OUT), IC6.1
unnamed: C12.2, IC4.5 (+IN), R24.2
unnamed: C14.1, IN2B.1
unnamed: C14.2, IC5.3 (+IN), R30.2
unnamed: C15.1, C18.2, G2P3B.1, IC5.1 (OUT)
unnamed: C18.1, G2P2B.1, IC5.2 (-IN)
unnamed: G2P1B.1, R31.2
unnamed: C15.2, IC5.5 (+IN), R26.2
unnamed: IC5.6 (-IN), IC5.7 (OUT), IC6.3
unnamed: IC6.4, R27.2, R28.2
unnamed: R27.1, R32.2 (S)
unnamed: IC6.6, R25.1, R29.2
unnamed: IC6.7, R23.1, R25.2
unnamed: OUTB.1, R23.2

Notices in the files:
parts and their libraries:
princeton-tech: Copyright (C) 2010, Bob Starr
